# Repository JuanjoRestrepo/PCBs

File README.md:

# PCBs
PCB Designs and Courses Repository

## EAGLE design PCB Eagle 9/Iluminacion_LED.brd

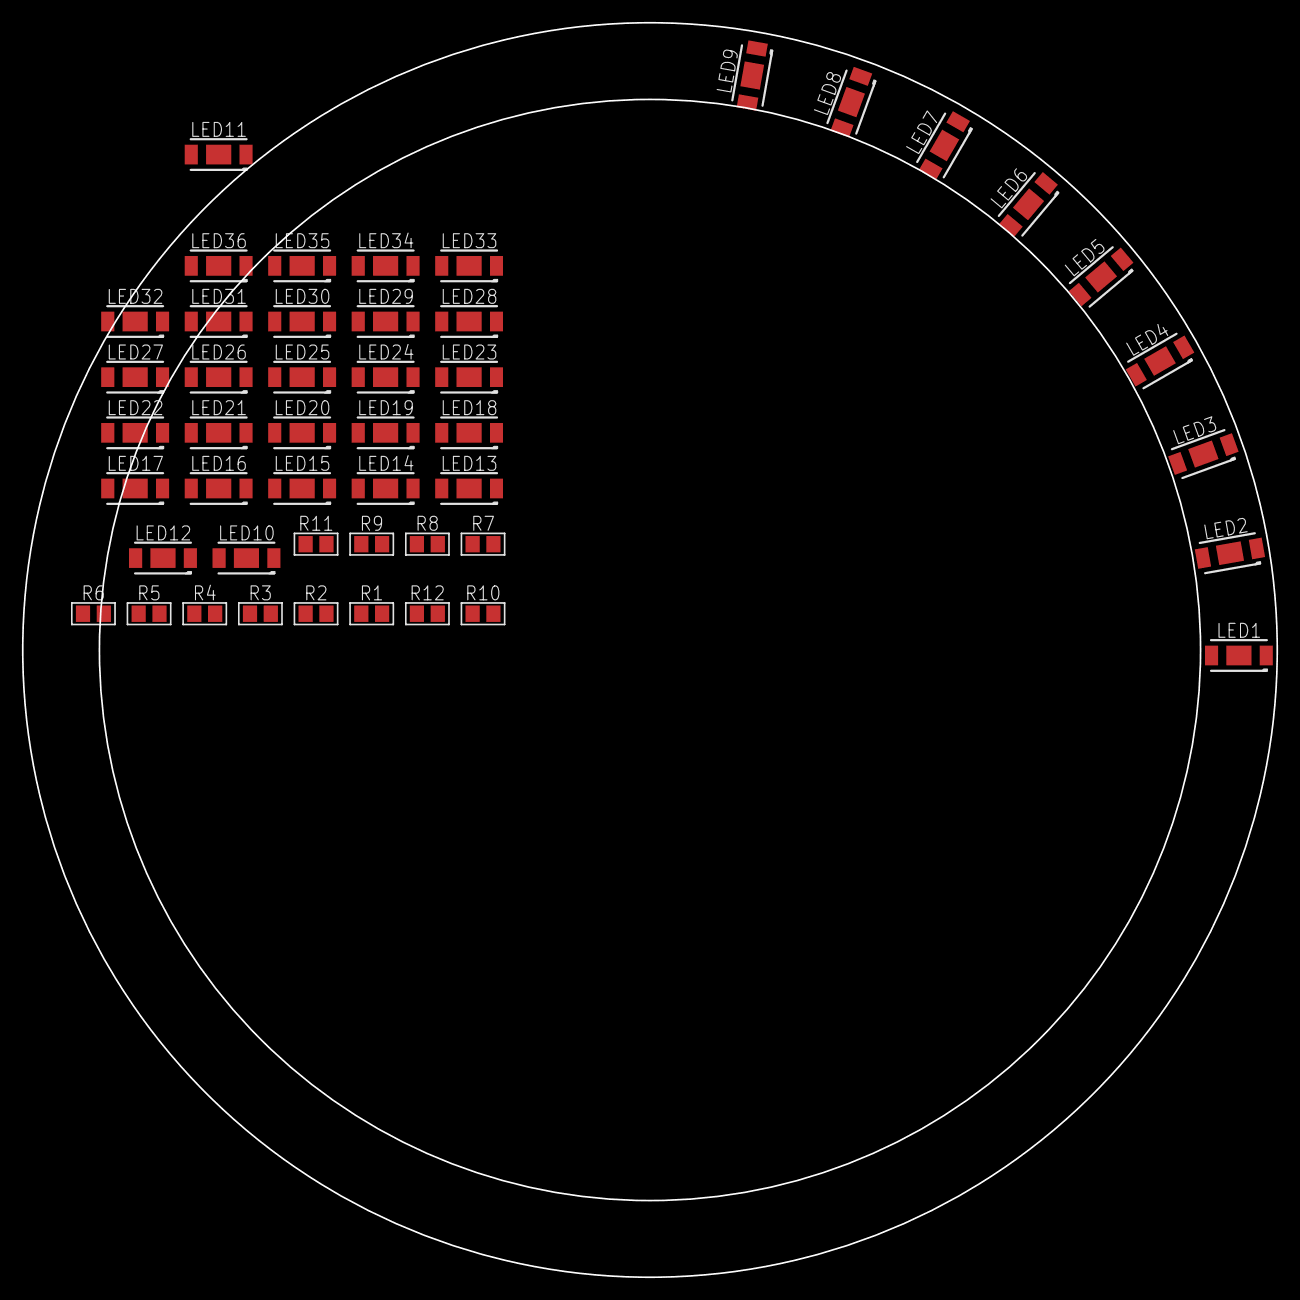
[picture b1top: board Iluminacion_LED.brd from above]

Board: 2 copper layers, 114.5 x 114.5 mm, 48 parts (0 on the bottom side), 16 nets, no tracks yet.

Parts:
LED1, LED2, LED3, LED4, LED5, LED6, LED7, LED8, LED9, LED10, LED11, LED12, LED13, LED14, LED15, LED16, LED17, LED18, LED19, LED20, LED21, LED22, LED23, LED24, LED25, LED26, LED27, LED28, LED29, LED30, LED31, LED32, LED33, LED34, LED35, LED36: LED5730-BLANCO
R1, R2, R3, R4, R5, R6, R7, R8, R9, R10, R11, R12: 1k; R0805

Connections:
+12V: R1.1, R3.1, R6.1, R8.1, R10.1, R12.1
GND: LED7.C, LED8.C, LED9.C, LED10.C, LED11.C, LED12.C, LED13.C, LED14.C, LED15.C, LED16.C, LED17.C, LED18.C, LED19.C, LED20.C, LED21.C, LED22.C, LED23.C, LED24.C
unnamed: LED22.A, LED23.A, LED24.A, R9.2
unnamed: LED16.A, LED17.A, LED18.A, R2.2
unnamed: LED1.A, LED2.A, LED3.A, R1.2
unnamed: LED4.A, LED5.A, LED6.A, R3.2
unnamed: LED19.A, LED20.A, LED21.A, R4.2
unnamed: LED25.A, LED26.A, LED27.A, R6.2
unnamed: LED7.A, LED8.A, LED9.A, R5.2
unnamed: LED10.A, LED11.A, LED12.A, R7.2
unnamed: LED28.A, LED29.A, LED30.A, R8.2
unnamed: LED34.A, LED35.A, LED36.A, R10.2
unnamed: LED13.A, LED14.A, LED15.A, R11.2
unnamed: LED31.A, LED32.A, LED33.A, R12.2
X1: LED1.C, LED2.C, LED3.C, LED4.C, LED5.C, LED6.C, LED34.C, LED35.C, LED36.C, R2.1, R4.1, R9.1
Y1: LED25.C, LED26.C, LED27.C, LED28.C, LED29.C, LED30.C, LED31.C, LED32.C, LED33.C, R5.1, R7.1

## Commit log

2024-04-01 First Commit
    PCB Eagle 9 Course
